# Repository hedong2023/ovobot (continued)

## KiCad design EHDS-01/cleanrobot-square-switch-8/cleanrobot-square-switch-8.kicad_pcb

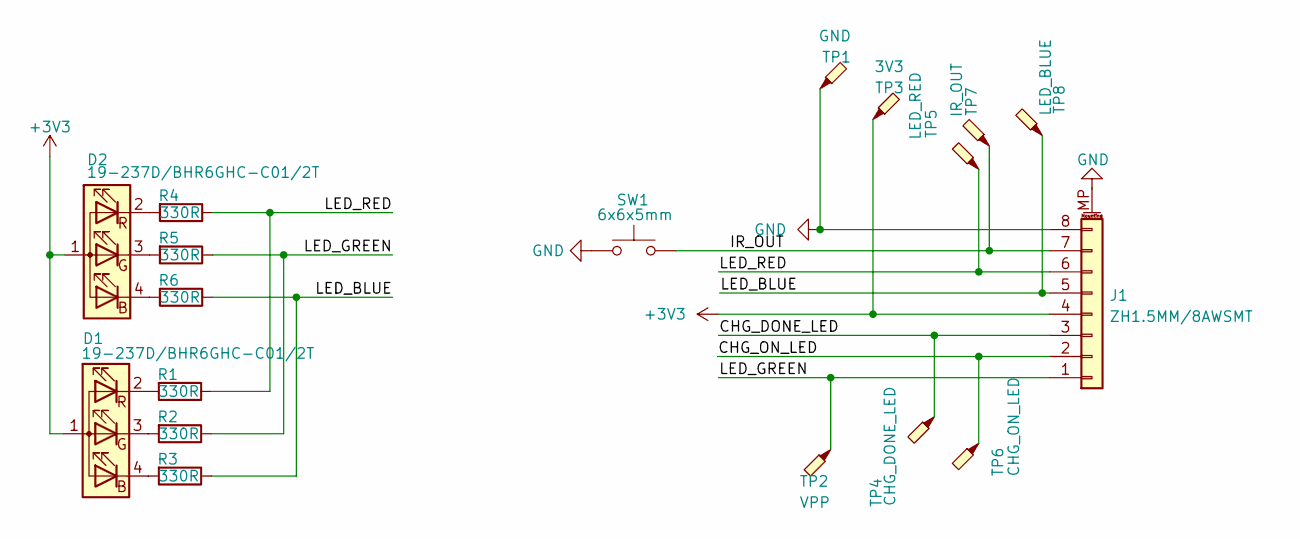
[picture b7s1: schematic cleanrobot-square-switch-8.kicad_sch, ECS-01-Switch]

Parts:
D1, D2: 19-237D/BHR6GHC-C01/2T; LED_Everlight_ARGB_1.6x1.6mm
J1: ZH1.5MM/8AWSMT; JST_ZH_S8B-ZR-SM4-TF_1x08-1MP_P1.50mm_Horizontal
R1, R2, R3, R4, R5, R6: 330R; R_0603_1608Metric
SW1: 6x6x5mm; SW_Push_1P1T_NO_6x6mm_H5.0mm
TP1: GND; TestPoint_Pad_D1.0mm
TP2: VPP; TestPoint_Pad_D1.0mm
TP3: 3V3; TestPoint_Pad_D1.0mm
TP4: CHG_DONE_LED; TestPoint_Pad_D1.0mm
TP5: LED_RED; TestPoint_Pad_D1.0mm
TP6: CHG_ON_LED; TestPoint_Pad_D1.0mm
TP7: IR_OUT; TestPoint_Pad_D1.0mm
TP8: LED_BLUE; TestPoint_Pad_D1.0mm

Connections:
+3V3: D1.1 (A), D2.1 (A), J1.4, TP3.1
/CHG_DONE_LED: J1.3, TP4.1
/CHG_ON_LED: J1.2, TP6.1
/IR_OUT: J1.7, SW1.2, TP7.1
/LED_BLUE: J1.5, R3.1, R6.1, TP8.1
/LED_GREEN: J1.1, R2.1, R5.1, TP2.1
/LED_RED: J1.6, R1.1, R4.1, TP5.1
GND: J1.8, J1.MP (MountPin), SW1.1, TP1.1
unnamed: D1.4 (BK), R3.2
unnamed: D1.3 (GK), R2.2
unnamed: D1.2 (RK), R1.2
unnamed: D2.4 (BK), R6.2
unnamed: D2.3 (GK), R5.2
unnamed: D2.2 (RK), R4.2

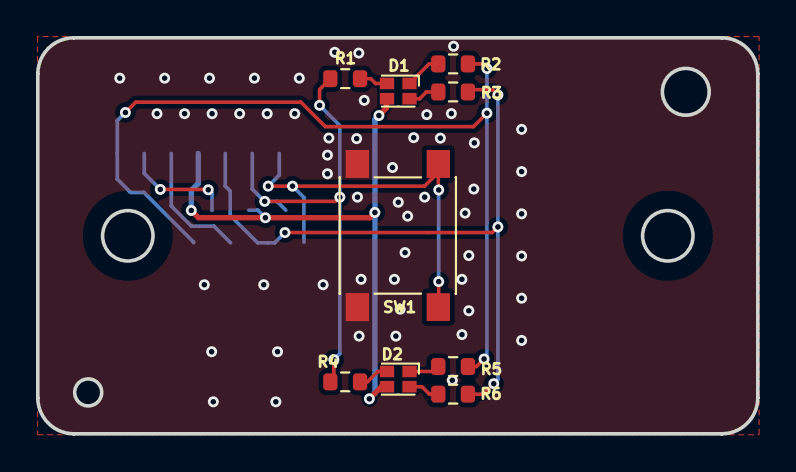
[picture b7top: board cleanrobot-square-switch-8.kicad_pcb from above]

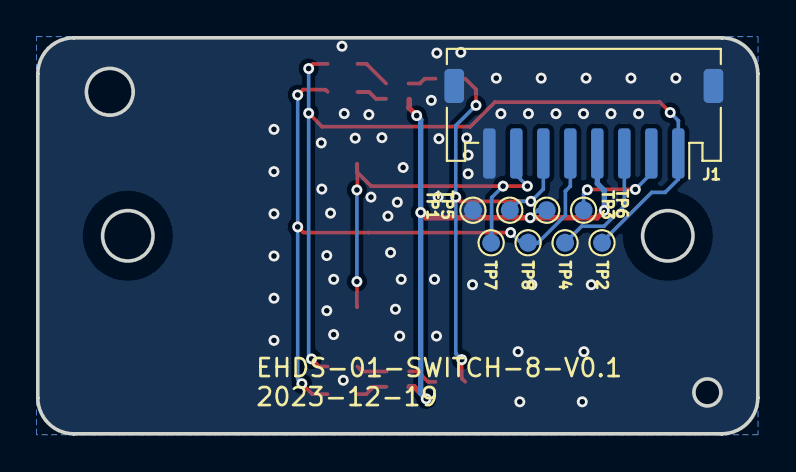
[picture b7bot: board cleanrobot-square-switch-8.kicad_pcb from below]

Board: 2 copper layers, 40.0 x 22.0 mm, 18 parts (9 on the bottom side), 14 nets.
